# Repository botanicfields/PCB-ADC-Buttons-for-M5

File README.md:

# PCB-ADC-Button-for-M5
a PCB converts 5 buttons into 1 analog output

# M5 用光センサ・押しボタン 5 基板
## Ambient Light Sensor and 5 Buttons for M5

### 委託販売: スイッチサイエンス

https://www.switch-science.com/catalog/7227/

# 1. 特徴

- 周囲の明るさをアナログ電圧で出力します
- 押しボタン 5 個の操作を、1 本のアナログ電圧で出力します
- GROVE コネクタで接続します
- 出力レベルは 0 ~ 3.3V で、M5(ESP32) の GPIO に合わせています
- 電源は 5V で、M5シリーズの GROVE コネクタに合わせています
- JC_Button と同等の判定を可能とするプログラムを用意しています
- 手に持つことを考慮し、スルーホール部品を使用していません
- センサーへの影響を考慮し、パイロットランプはありません。

# 2. 注意
- 押しボタンスイッチのチャタリングや接触抵抗による誤動作が皆無とは言えません。時刻の設定など、結果を確認しながら操作し、やり直しを可能とするなど、運用でカバーできる範囲でご利用ください。

- 複数ボタンの同時押しの判定はできません。

- M5Stack Basic の GROVE コネクタに直結して使用することはできません。
「GROVE-ジャンパケーブル」などを用いて、アナログ入力の GPIO および 5V, GND に接続する必要があります。

「GROVE - 4ピン - ジャンパオスケーブル（5本セット）」

https://www.switch-science.com/catalog/6245/)

「GROVE - 4ピン-ジャンパメスケーブル (5本セット)」

https://www.switch-science.com/catalog/1048/

M5Stack Basic で、G35, G36, 5V, GND に接続した例

## M5 シリーズの GROVE ポート

　M5 シリーズ (ESP32) では、アナログ入力として一般に G32 ～ G39 が使用されます。
G2, G4, G12 ~ G15, G24 ~ G26 のアナログ入力機能は、Wi-Fi 等が使用しますので
一般には使いづらいです。G0 はプルアップがあるなどアナログ入力には向きません。

| モデル | GROVE | 主な用途 |
|:-:|:-:|:-:|
| M5Stack Basic| G22, G21 | I2C |
| M5Stack Core2| G33, G32 | I2C, I/O, UART |
| M5StickC | G33, G32 | I2C, I/O, UART |
| M5Atom | G32, G26 | I2C, I/O, UART |

# 3. 内容

## 光センサ
Everlight ALS-PT19

https://jp.everlight.com/wp-content/plugins/ItemRelationship/product_files/pdf/ALS-PT19-315C-L177-TR8_V8.pdf

## ソフトウェア

### (1) BF_AdcButton.h, BF_Adc_Button.cpp
光センサの出力を読み出すプログラム、および 5 個の押しボタンの状態を読み出すプログラムです。JC_Button を流用・改変しています。

https://github.com/JChristensen/JC_Button

### (2) BF_AdcButtonTest.h, BF_Adc_ButtonTest.cpp
上記コードを呼び出すテスト用のプログラムです。

### (3) BF-028.ino
上記テストプログラムのメインプログラムです。

# 4. 解説
Qiita 「ESP32 のアナログ入力で、押しボタン 5 個を判別する」

https://qiita.com/BotanicFields/items/15d8d45836a4d2f6c87a

# 5. 接続例
「RGB LED 276 for M5Atom」への接続例です。

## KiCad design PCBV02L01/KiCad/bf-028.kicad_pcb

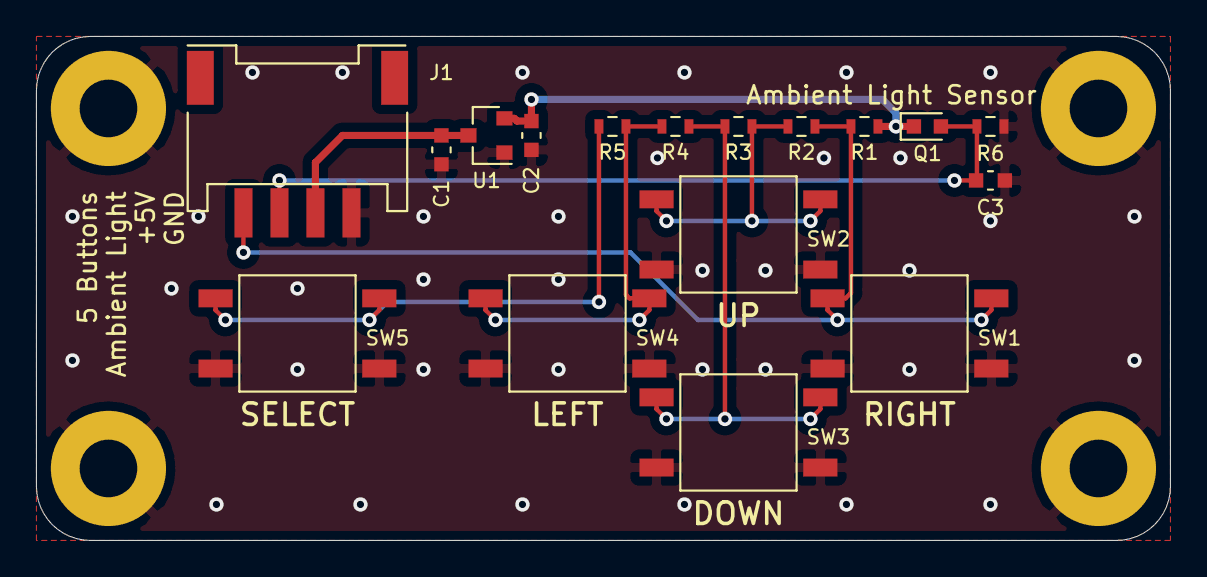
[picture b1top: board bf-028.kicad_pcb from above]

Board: 2 copper layers, 63.0 x 28.0 mm, 17 parts (0 on the bottom side), 9 nets.

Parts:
C1, C2: 1u; BF_C_0603_1608Metric
C3: 0.1u; BF_C_0603_1608Metric
J1: Analog; HW4-SMD-2.0-90D
Q1: ALS-PT19; BF@ALS-PT19_0603_1608Metric
R1: 3.3k; BF_R_0603_1608Metric
R2, R3: 1k; BF_R_0603_1608Metric
R4: 1.5k; BF_R_0603_1608Metric
R5: 5.1k; BF_R_0603_1608Metric
R6: 10k; BF_R_0603_1608Metric
SW1: RIGHT; BF@K2-6639SP
SW2: UP; BF@K2-6639SP
SW3: DOWN; BF@K2-6639SP
SW4: LEFT; BF@K2-6639SP
SW5: SELECT; BF@K2-6639SP
U1: XC6206P332MR; SOT-23

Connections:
/A0: J1.1, R1.2, R2.1, SW1.1
/A1: C3.1, J1.2, Q1.2, R6.1
GND: C1.2, C2.2, C3.2, J1.4, R6.2, SW1.2, SW2.2, SW3.2, SW4.2, SW5.2, U1.1
unnamed: C1.1, J1.3, U1.3
unnamed: C2.1, Q1.1, R1.1, U1.2
unnamed: R2.2, R3.1, SW2.1
unnamed: R3.2, R4.1, SW3.1
unnamed: R4.2, R5.1, SW4.1
unnamed: R5.2, SW5.1

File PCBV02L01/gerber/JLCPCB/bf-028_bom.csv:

Comment,Designator,Footprint,LCSC
1u,"C1,C2",bf:BF_C_0603_1608Metric,C15849
0.1u,C3,bf:BF_C_0603_1608Metric,C14663
Analog,J1,OPL_Connector:HW4-SMD-2.0-90D,
ALS-PT19,Q1,bf:BF@ALS-PT19_0603_1608Metric,C146233
3.3k,R1,bf:BF_R_0603_1608Metric,C22978
1k,"R2,R3",bf:BF_R_0603_1608Metric,C21190
1.5k,R4,bf:BF_R_0603_1608Metric,C22843
5.1k,R5,bf:BF_R_0603_1608Metric,C23186
10k,R6,bf:BF_R_0603_1608Metric,C25804
RIGHT,SW1,bf:BF@K2-6639SP,C83206
UP,SW2,bf:BF@K2-6639SP,C83206
DOWN,SW3,bf:BF@K2-6639SP,C83206
LEFT,SW4,bf:BF@K2-6639SP,C83206
SELECT,SW5,bf:BF@K2-6639SP,C83206
XC6206P332MR,U1,Package_TO_SOT_SMD:SOT-23,C5446

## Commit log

2021-05-29 first revision
2021-05-30 Update README.md
    new
2021-05-30 photo
    add photos
2021-05-30 Update README.md
    add image
2021-05-30 add doc
    move pdf to root
2021-06-04 Update README.md
    add Switch Science Market Place
2021-06-05 Update README.md
    GROVE of M5 Series
2021-06-05 Update BF-028.ino
    Add M5StickC, Change GPIO
2021-06-05 readme.md
    Add M5Stack image
2021-12-18 Update BF-028.ino
    add unsigned to "int last_ms"

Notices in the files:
PCBV02L01/KiCad/bf-028.kicad_pcb:
Copyright 2021 BotanicFields, Inc.
